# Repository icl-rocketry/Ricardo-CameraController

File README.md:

# Ricardo-CameraController
The CM5 (Compute Module 5) carrier board for cameras on rocket

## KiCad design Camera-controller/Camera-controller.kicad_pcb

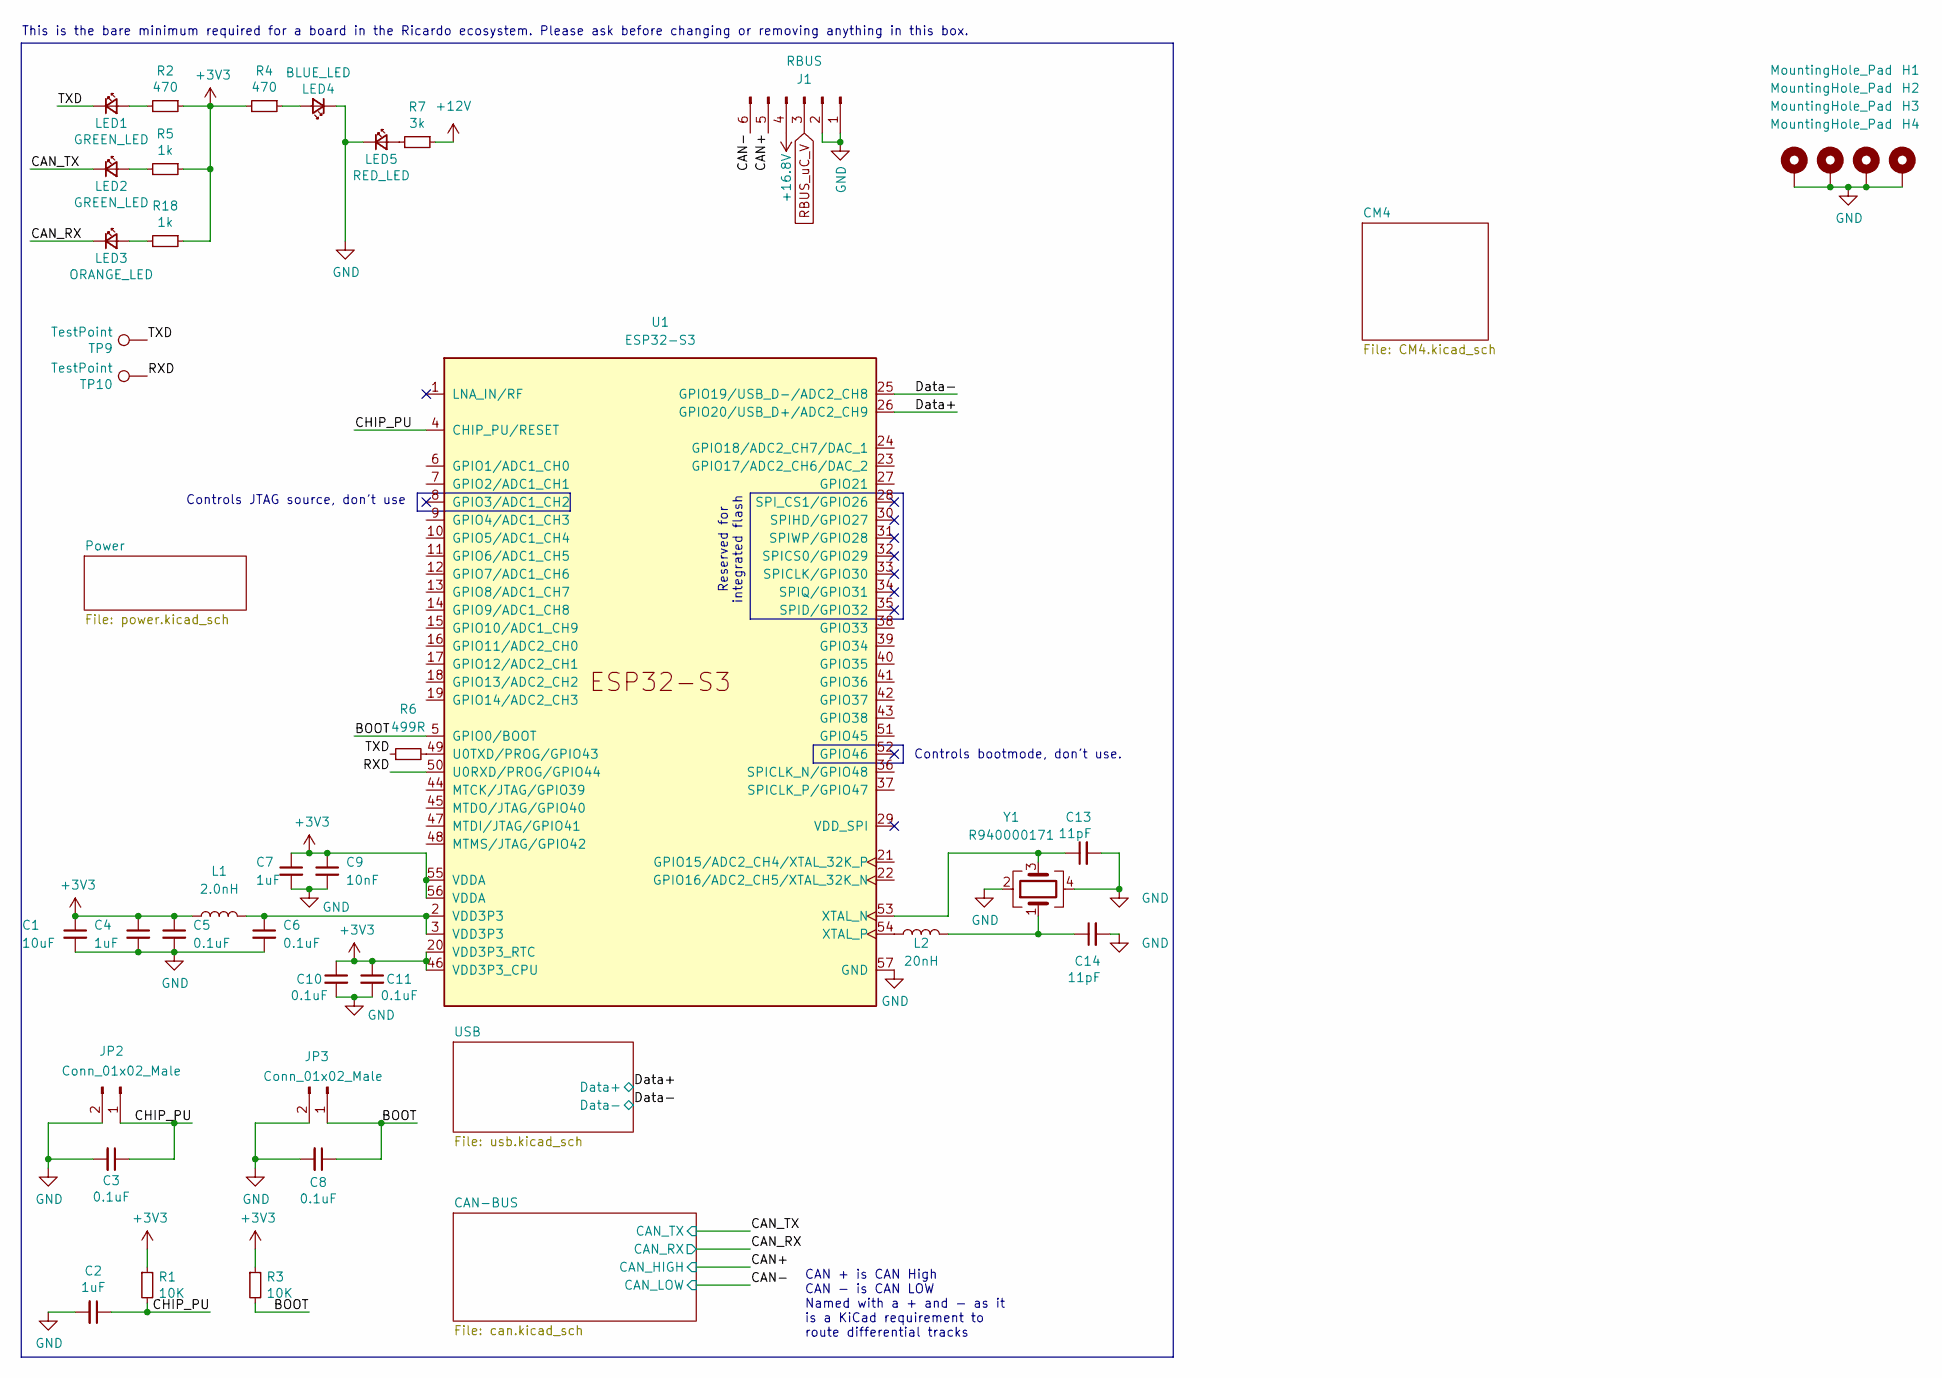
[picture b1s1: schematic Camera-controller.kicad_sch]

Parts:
C1: 10uF; C_0402_1005Metric
C2, C4, C7: 1uF; C_0402_1005Metric
C3, C5, C6, C8, C10, C11: 0.1uF; C_0402_1005Metric
C9: 10nF; C_0402_1005Metric
C13, C14: 11pF; C_0402_1005Metric
H1, H2, H3, H4: MountingHole_Pad; MountingHole_3.2mm_M3_DIN965_Pad
J1: RBUS; Molex_Mini-Fit_Jr_5569-06A2_2x03_P4.20mm_Horizontal
JP2, JP3: Conn_01x02_Male; PinHeader_1x02_P2.54mm_Vertical
L1: 2.0nH; L_0402_1005Metric
L2: 20nH; L_0402_1005Metric
LED1, LED2: GREEN_LED; LED_0402_1005Metric
LED3: ORANGE_LED; LED_0402_1005Metric
LED4: BLUE_LED; LED_0402_1005Metric
LED5: RED_LED; LED_0402_1005Metric
R1, R3: 10K; R_0402_1005Metric
R2, R4: 470; R_0402_1005Metric
R5, R18: 1k; R_0402_1005Metric
R6: 499R; R_0402_1005Metric
R7: 3k; R_0402_1005Metric
TP9, TP10: TestPoint; TestPoint_Pad_D1.0mm
U1: ESP32-S3; QFN40P700X700X90-57N
Y1: R940000171; Crystal_SMD_2016-4Pin_2.0x1.6mm

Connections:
+3V3: C1.1, C4.1, C5.1, C7.1, C9.1, C10.1, C11.1, L1.1, R1.1, R2.1, R3.1, R4.2, R5.1, R18.1, U1.20 (VDD3P3_RTC), U1.46 (VDD3P3_CPU), U1.55 (VDDA), U1.56 (VDDA); also elsewhere on the board
+12V: R7.1
/BOOT: C8.1, JP3.1, R3.2, U1.5 (GPIO0/BOOT)
/CAN+: J1.5; also elsewhere on the board
/CAN-: J1.6; also elsewhere on the board
/CAN_RX: LED3.1 (K); also elsewhere on the board
/CAN_TX: LED2.1 (K); also elsewhere on the board
/CHIP_PU: C2.1, C3.1, JP2.1, R1.2, U1.4 (CHIP_PU/RESET)
/Data+: U1.26 (GPIO20/USB_D+/ADC2_CH9); also elsewhere on the board
/Data-: U1.25 (GPIO19/USB_D-/ADC2_CH8); also elsewhere on the board
/RXD: TP10.1, U1.50 (U0RXD/PROG/GPIO44)
/TXD: LED1.1 (K), R6.1, TP9.1
unnamed: C6.1, L1.2, U1.2 (VDD3P3), U1.3 (VDD3P3)
unnamed: C14.1, L2.2, Y1.1
unnamed: LED1.2 (A), R2.2
unnamed: LED2.2 (A), R5.2
unnamed: LED3.2 (A), R18.2
unnamed: LED4.2 (A), R4.1
unnamed: LED5.2 (A), R7.2
unnamed: R6.2, U1.49 (U0TXD/PROG/GPIO43)
unnamed: C13.1, U1.53 (XTAL_N), Y1.3
unnamed: L2.1, U1.54 (XTAL_P)
RBUS_uC_V: J1.3; also elsewhere on the board

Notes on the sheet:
Controls bootmode, don't use.
This is the bare minimum required for a board in the Ricardo ecosystem. Please ask before changing or removing anything in this box.
CAN + is CAN High CAN - is CAN LOW Named with a + and - as it is a KiCad requirement to route differential tracks
Controls JTAG source, don't use
Reserved for integrated flash

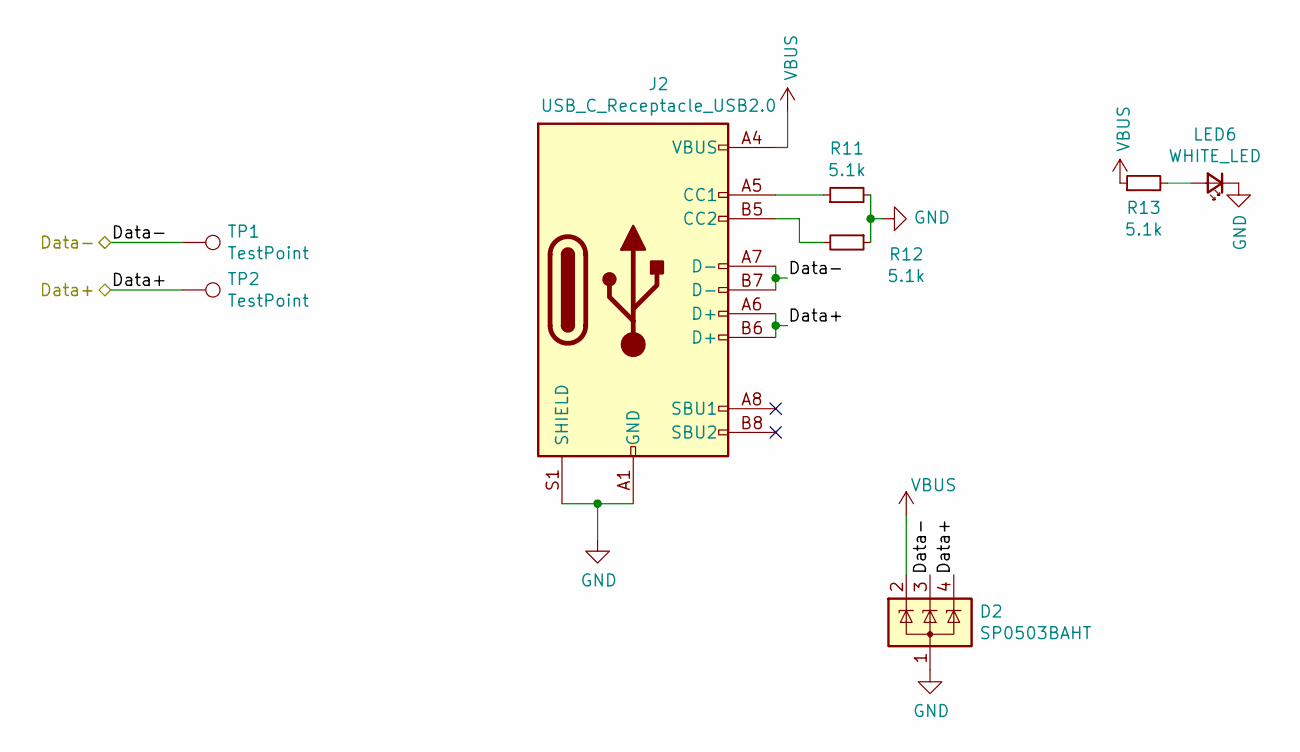
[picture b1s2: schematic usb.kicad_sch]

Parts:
D2: SP0503BAHT; SOT-143
J2: USB_C_Receptacle_USB2.0; USB_C_Receptacle_Palconn_UTC16-G
LED6: WHITE_LED; LED_0402_1005Metric
R11, R12, R13: 5.1k; R_0402_1005Metric
TP1, TP2: TestPoint; TestPoint_Pad_D1.0mm

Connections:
/Data+: D2.4 (K), J2.A6 (D+), J2.B6 (D+), TP2.1; also elsewhere on the board
/Data-: D2.3 (K), J2.A7 (D-), J2.B7 (D-), TP1.1; also elsewhere on the board
unnamed: J2.A5 (CC1), R11.1
unnamed: J2.B5 (CC2), R12.2
unnamed: LED6.2 (A), R13.2

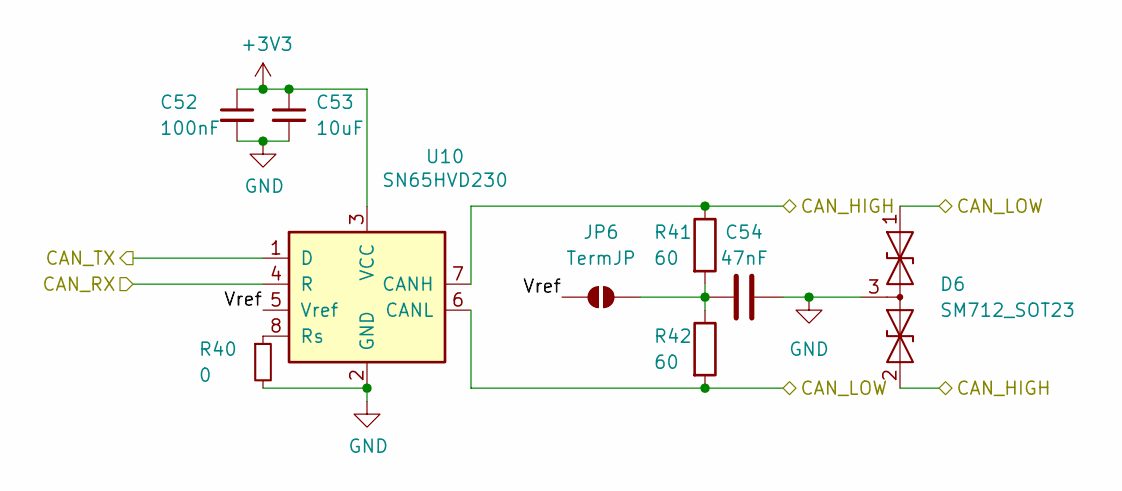
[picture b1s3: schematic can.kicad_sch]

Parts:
C52: 100nF; C_0402_1005Metric
C53: 10uF; C_0402_1005Metric
C54: 47nF; C_0402_1005Metric
D6: SM712_SOT23; SOT-23
JP6: TermJP; SmallerSolderJP
R40: 0; R_0603_1608Metric
R41, R42: 60; R_0603_1608Metric
U10: SN65HVD230; SOIC-8_3.9x4.9mm_P1.27mm

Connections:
unnamed 187: U10.1 (BST); also elsewhere on the board
unnamed 188: D6.1 (A1), R42.2, U10.6 (COMP); also elsewhere on the board
unnamed 189: U10.4 (SS); also elsewhere on the board

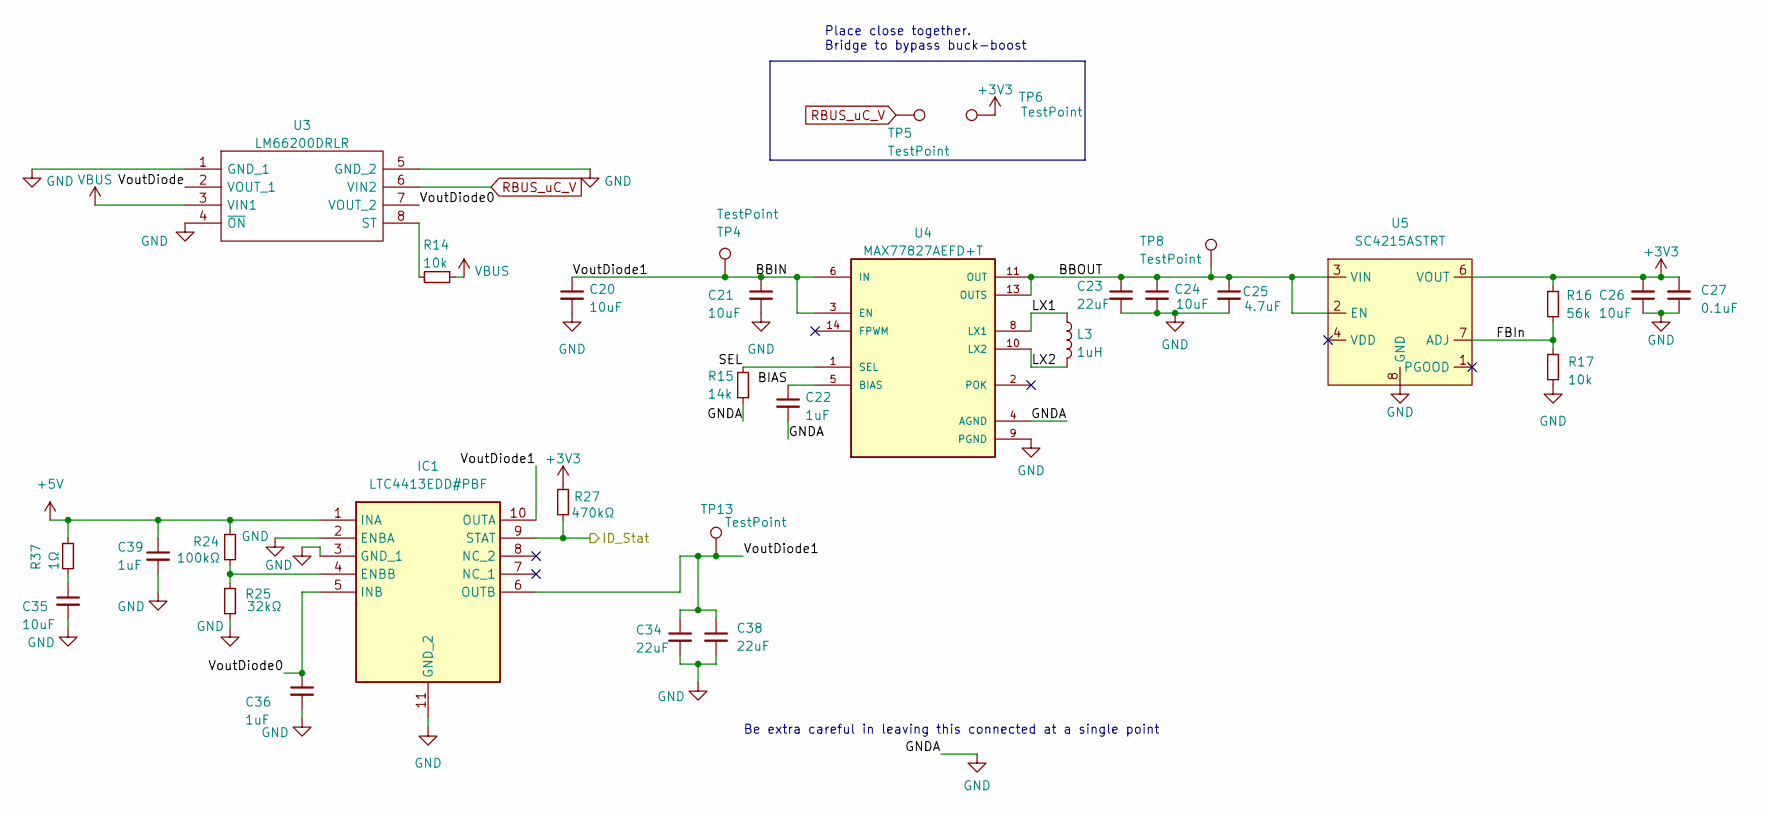
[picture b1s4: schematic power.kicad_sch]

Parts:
C20, C24, C26, C35: 10uF; C_0402_1005Metric
C21: 10uF; C_0603_1608Metric
C22, C36, C39: 1uF; C_0402_1005Metric
C23: 22uF; C_0603_1608Metric
C25: 4.7uF; C_0402_1005Metric
C27: 0.1uF; C_0402_1005Metric
C34, C38: 22uF; C_0402_1005Metric
IC1: LTC4413EDD#PBF; SON50P300X300X80-11N-D; Mouser Part Number 584-LTC4413EDD#PBF
L3: 1uH; L_0805_2012Metric
R14, R17: 10k; R_0402_1005Metric
R15: 14k; R_0402_1005Metric
R16: 56k; R_0402_1005Metric
R24: 100kΩ; R_0402_1005Metric
R25: 32kΩ; R_0402_1005Metric
R27: 470kΩ; R_0402_1005Metric
R37: 1Ω; R_0402_1005Metric
TP4, TP5, TP6, TP8: TestPoint; TestPoint_Pad_D1.5mm
TP13: TestPoint; TestPoint_Pad_D1.0mm
U3: LM66200DRLR; SOTFL50P160X60-8N; Manufacturer_Part_Number LM66200DRLR; Mouser Part Number 595-LM66200DRLR
U4: MAX77827AEFD+T; CONV_MAX77827AEFD+T; PARTREV B
U5: SC4215ASTRT; SOIC127P599X175-9N

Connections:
+3V3: C26.2, C27.2, R16.1, R27.1, TP6.1, U5.6 (VOUT); also elsewhere on the board
/Power/BBIN: C20.1, C21.1, C34.1, C38.1, IC1.6 (OUTB), IC1.10 (OUTA), TP4.1, TP13.1, U4.3 (EN), U4.6 (IN)
/Power/BBOUT: C23.1, C24.1, C25.1, TP8.1, U4.11 (OUT), U4.13 (OUTS), U5.2 (EN), U5.3 (VIN)
/Power/BIAS: C22.1, U4.5 (BIAS)
/Power/FBIn: R16.2, R17.1, U5.7 (ADJ)
/Power/ID_Stat: IC1.9 (STAT), R27.2
/Power/LX1: L3.1, U4.8 (LX1)
/Power/LX2: L3.2, U4.10 (LX2)
/Power/SEL: R15.1, U4.1 (SEL)
/Power/VoutDiode: U3.2 (VOUT_1)
/Power/VoutDiode0: C36.1, IC1.5 (INB), U3.7 (VOUT_2)
unnamed: C35.1, R37.2
unnamed: IC1.4 (ENBB), R24.2, R25.1
unnamed: R14.2, U3.8 (ST)
RBUS_uC_V: TP5.1, U3.6 (VIN2); also elsewhere on the board

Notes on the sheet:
Place close together. Bridge to bypass buck-boost
Be extra careful in leaving this connected at a single point

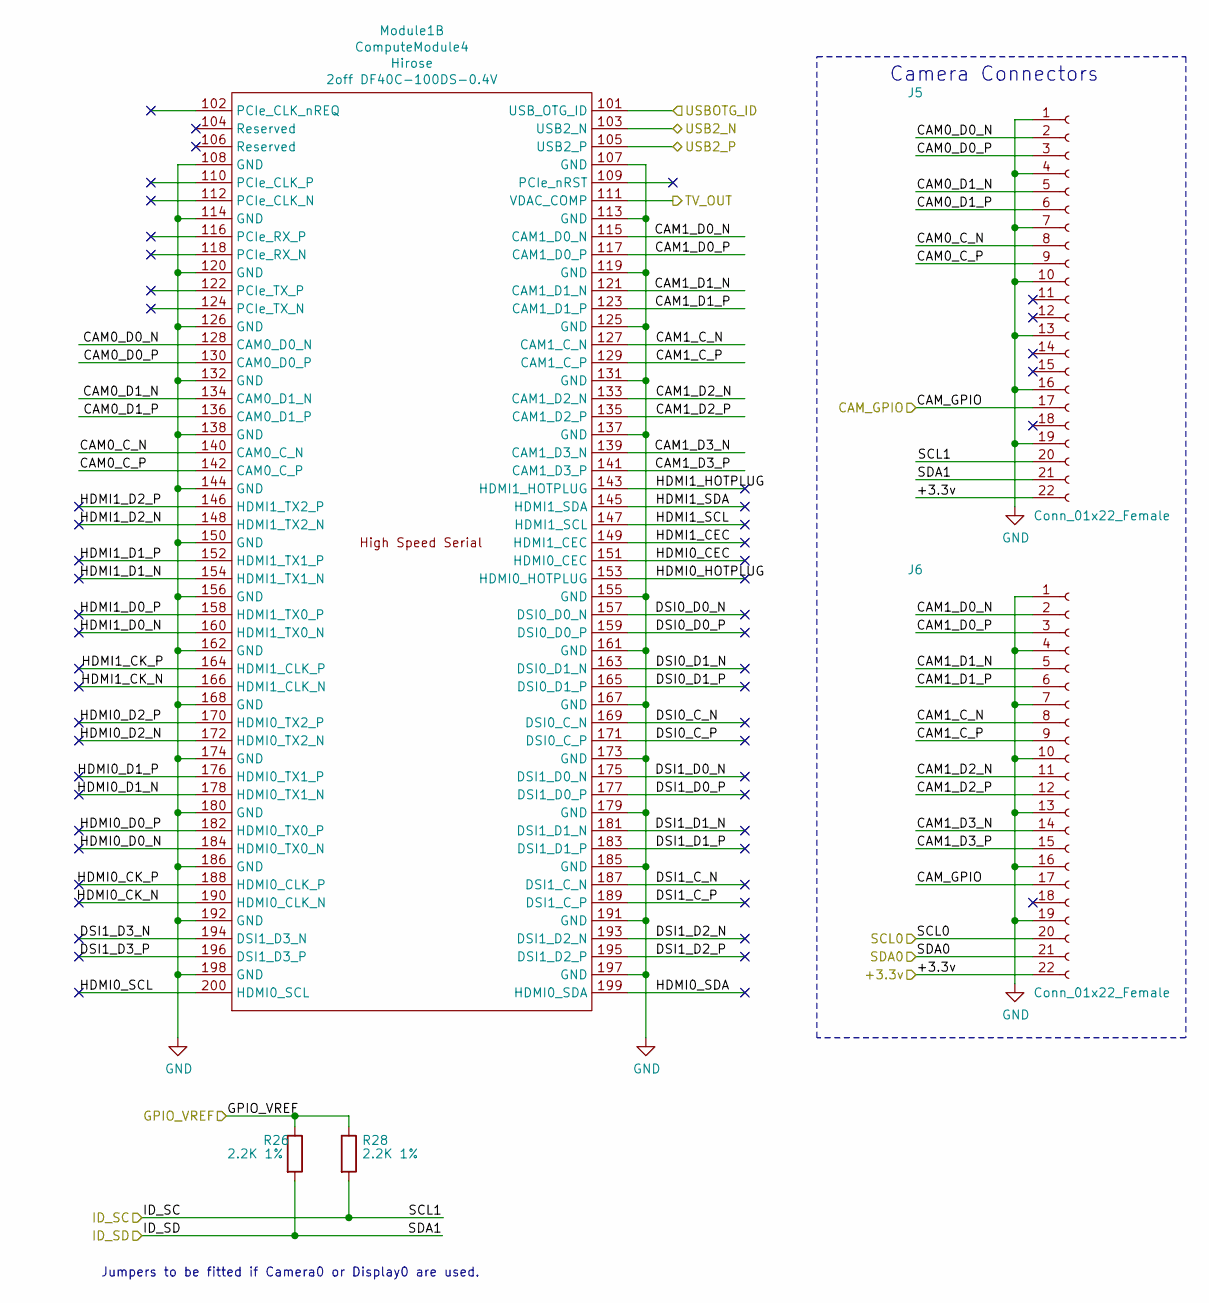
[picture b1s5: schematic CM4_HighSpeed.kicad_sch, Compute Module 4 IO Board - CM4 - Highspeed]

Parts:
J5, J6: Conn_01x22_Female; Hirose_FH12-22S-0.5SH_1x22-1MP_P0.50mm_Horizontal; Part Description 22 Position FFC, FPC Connector Contacts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
Module1: ComputeModule4; Raspberry-Pi-4-Compute-Module; Part Description 100 Position Connector Receptacle, Cent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
R26, R28: 2.2K 1%; R_0402_1005Metric; Part Description Resistor 2.2K M1005 1% 63mW

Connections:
/CM4/+3.3v: J5.22, J6.22; also elsewhere on the board
/CM4/CM4 _HighSpeed/CAM0_C_N: J5.8, Module1.140 (CAM0_C_N)
/CM4/CM4 _HighSpeed/CAM0_C_P: J5.9, Module1.142 (CAM0_C_P)
/CM4/CM4 _HighSpeed/CAM0_D0_N: J5.2, Module1.128 (CAM0_D0_N)
/CM4/CM4 _HighSpeed/CAM0_D0_P: J5.3, Module1.130 (CAM0_D0_P)
/CM4/CM4 _HighSpeed/CAM0_D1_N: J5.5, Module1.134 (CAM0_D1_N)
/CM4/CM4 _HighSpeed/CAM0_D1_P: J5.6, Module1.136 (CAM0_D1_P)
/CM4/CM4 _HighSpeed/CAM1_C_N: J6.8, Module1.127 (CAM1_C_N)
/CM4/CM4 _HighSpeed/CAM1_C_P: J6.9, Module1.129 (CAM1_C_P)
/CM4/CM4 _HighSpeed/CAM1_D0_N: J6.2, Module1.115 (CAM1_D0_N)
/CM4/CM4 _HighSpeed/CAM1_D0_P: J6.3, Module1.117 (CAM1_D0_P)
/CM4/CM4 _HighSpeed/CAM1_D1_N: J6.5, Module1.121 (CAM1_D1_N)
/CM4/CM4 _HighSpeed/CAM1_D1_P: J6.6, Module1.123 (CAM1_D1_P)
/CM4/CM4 _HighSpeed/CAM1_D2_N: J6.11, Module1.133 (CAM1_D2_N)
/CM4/CM4 _HighSpeed/CAM1_D2_P: J6.12, Module1.135 (CAM1_D2_P)
/CM4/CM4 _HighSpeed/CAM1_D3_N: J6.14, Module1.139 (CAM1_D3_N)
/CM4/CM4 _HighSpeed/CAM1_D3_P: J6.15, Module1.141 (CAM1_D3_P)
/CM4/CM4 _HighSpeed/CAM_GPIO: J5.17, J6.17; also elsewhere on the board
/CM4/CM4 _HighSpeed/DSI0_C_N: Module1.169 (DSI0_C_N)
/CM4/CM4 _HighSpeed/DSI0_C_P: Module1.171 (DSI0_C_P)
/CM4/CM4 _HighSpeed/DSI0_D0_N: Module1.157 (DSI0_D0_N)
/CM4/CM4 _HighSpeed/DSI0_D0_P: Module1.159 (DSI0_D0_P)
/CM4/CM4 _HighSpeed/DSI0_D1_N: Module1.163 (DSI0_D1_N)
/CM4/CM4 _HighSpeed/DSI0_D1_P: Module1.165 (DSI0_D1_P)
/CM4/CM4 _HighSpeed/DSI1_C_N: Module1.187 (DSI1_C_N)
/CM4/CM4 _HighSpeed/DSI1_C_P: Module1.189 (DSI1_C_P)
/CM4/CM4 _HighSpeed/DSI1_D0_N: Module1.175 (DSI1_D0_N)
/CM4/CM4 _HighSpeed/DSI1_D0_P: Module1.177 (DSI1_D0_P)
/CM4/CM4 _HighSpeed/DSI1_D1_N: Module1.181 (DSI1_D1_N)
/CM4/CM4 _HighSpeed/DSI1_D1_P: Module1.183 (DSI1_D1_P)
/CM4/CM4 _HighSpeed/DSI1_D2_N: Module1.193 (DSI1_D2_N)
/CM4/CM4 _HighSpeed/DSI1_D2_P: Module1.195 (DSI1_D2_P)
/CM4/CM4 _HighSpeed/DSI1_D3_N: Module1.194 (DSI1_D3_N)
/CM4/CM4 _HighSpeed/DSI1_D3_P: Module1.196 (DSI1_D3_P)
/CM4/CM4 _HighSpeed/GPIO_VREF: R26.1, R28.1; also elsewhere on the board
/CM4/CM4 _HighSpeed/HDMI0_CEC: Module1.151 (HDMI0_CEC)
/CM4/CM4 _HighSpeed/HDMI0_CK_N: Module1.190 (HDMI0_CLK_N)
/CM4/CM4 _HighSpeed/HDMI0_CK_P: Module1.188 (HDMI0_CLK_P)
/CM4/CM4 _HighSpeed/HDMI0_D0_N: Module1.184 (HDMI0_TX0_N)
/CM4/CM4 _HighSpeed/HDMI0_D0_P: Module1.182 (HDMI0_TX0_P)
/CM4/CM4 _HighSpeed/HDMI0_D1_N: Module1.178 (HDMI0_TX1_N)
/CM4/CM4 _HighSpeed/HDMI0_D1_P: Module1.176 (HDMI0_TX1_P)
/CM4/CM4 _HighSpeed/HDMI0_D2_N: Module1.172 (HDMI0_TX2_N)
/CM4/CM4 _HighSpeed/HDMI0_D2_P: Module1.170 (HDMI0_TX2_P)
/CM4/CM4 _HighSpeed/HDMI0_HOTPLUG: Module1.153 (HDMI0_HOTPLUG)
/CM4/CM4 _HighSpeed/HDMI0_SCL: Module1.200 (HDMI0_SCL)
/CM4/CM4 _HighSpeed/HDMI0_SDA: Module1.199 (HDMI0_SDA)
/CM4/CM4 _HighSpeed/HDMI1_CEC: Module1.149 (HDMI1_CEC)
/CM4/CM4 _HighSpeed/HDMI1_CK_N: Module1.166 (HDMI1_CLK_N)
/CM4/CM4 _HighSpeed/HDMI1_CK_P: Module1.164 (HDMI1_CLK_P)
/CM4/CM4 _HighSpeed/HDMI1_D0_N: Module1.160 (HDMI1_TX0_N)
/CM4/CM4 _HighSpeed/HDMI1_D0_P: Module1.158 (HDMI1_TX0_P)
/CM4/CM4 _HighSpeed/HDMI1_D1_N: Module1.154 (HDMI1_TX1_N)
/CM4/CM4 _HighSpeed/HDMI1_D1_P: Module1.152 (HDMI1_TX1_P)
/CM4/CM4 _HighSpeed/HDMI1_D2_N: Module1.148 (HDMI1_TX2_N)
/CM4/CM4 _HighSpeed/HDMI1_D2_P: Module1.146 (HDMI1_TX2_P)
/CM4/CM4 _HighSpeed/HDMI1_HOTPLUG: Module1.143 (HDMI1_HOTPLUG)
/CM4/CM4 _HighSpeed/HDMI1_SCL: Module1.147 (HDMI1_SCL)
/CM4/CM4 _HighSpeed/HDMI1_SDA: Module1.145 (HDMI1_SDA)
/CM4/CM4 _HighSpeed/ID_SC: J5.20, R28.2; also elsewhere on the board
/CM4/CM4 _HighSpeed/ID_SD: J5.21, R26.2; also elsewhere on the board
/CM4/CM4 _HighSpeed/SCL0: J6.20; also elsewhere on the board
/CM4/CM4 _HighSpeed/SDA0: J6.21; also elsewhere on the board
/CM4/CM4 _HighSpeed/USBOTG_ID: Module1.101 (USB_OTG_ID); also elsewhere on the board
/CM4/CM4_GPIO/TV_OUT: Module1.111 (VDAC_COMP); also elsewhere on the board
/CM4/CM4_USB/USB2_N: Module1.103 (USB2_N); also elsewhere on the board
/CM4/CM4_USB/USB2_P: Module1.105 (USB2_P); also elsewhere on the board

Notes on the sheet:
Jumpers to be fitted if Camera0 or Display0 are used.
Camera Connectors

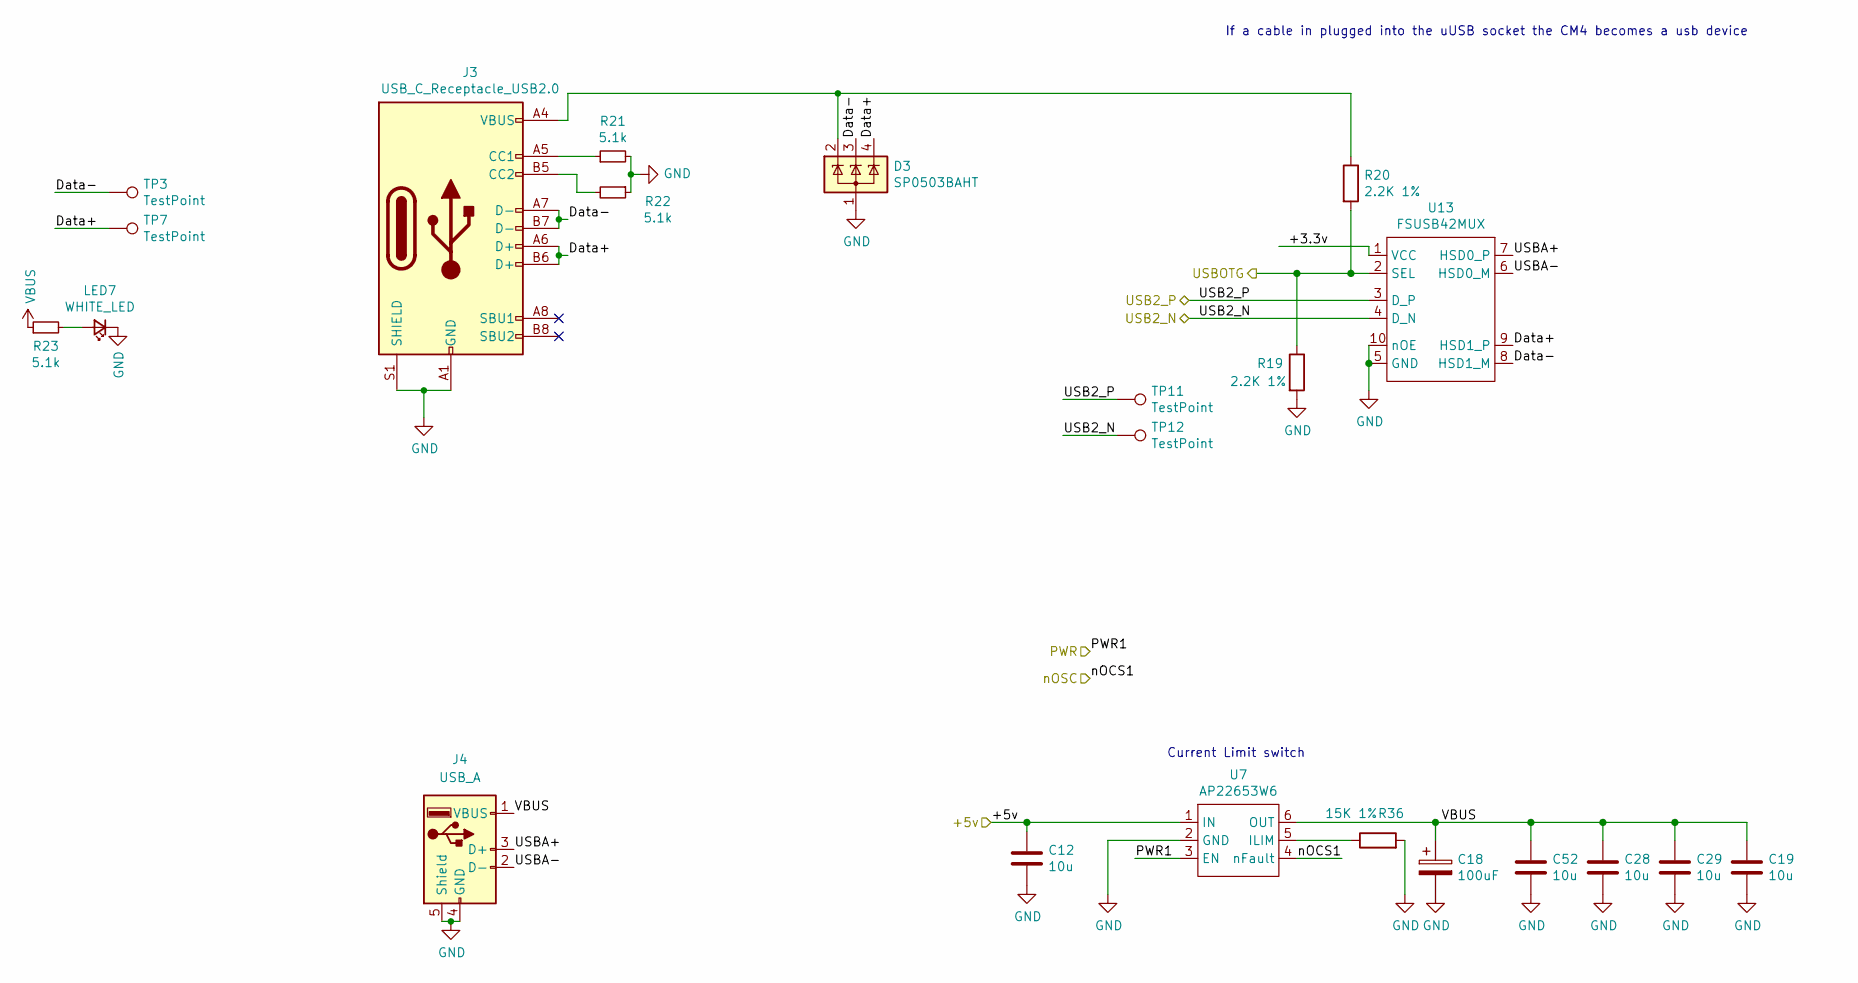
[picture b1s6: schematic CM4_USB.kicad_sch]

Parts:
C12, C19, C28, C29, C52: 10u; C_0805_2012Metric; Part Description 10uF 10% 10V Ceramic Capacitor X7R 0805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
C18: 100uF; CP_EIA-7343-31_Kemet-D; Part Description Capacitor, SP-Cap, 100u, 6.3V, 15mR ESR
D3: SP0503BAHT; SOT-143
J3: USB_C_Receptacle_USB2.0; USB_C_Receptacle_Palconn_UTC16-G
J4: USB_A; USB_A_Wuerth_614004134726_Horizontal
LED7: WHITE_LED; LED_0402_1005Metric
R19, R20: 2.2K 1%; R_0402_1005Metric; Part Description Resistor 2.2K M1005 1% 63mW
R21, R22, R23: 5.1k; R_0402_1005Metric
R36: 15K 1%; R_0402_1005Metric; Part Description Resistor 15K M1005 1% 63mW
TP3, TP7, TP11, TP12: TestPoint; TestPoint_Pad_D1.0mm
U7: AP22653W6; SOT-23-6; Part Description Power Switch/Driver 1:1 P-Channel 2.1A 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
U13: FSUSB42MUX; MSOP-10_3x3mm_P0.5mm; Part Description USB Switch IC 1 Channel 10-MSOP

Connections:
/CM4/CM4 _HighSpeed/USBOTG_ID: R19.1, R20.2, U13.2 (SEL); also elsewhere on the board
/CM4/CM4_USB/+3.3v: U13.1 (VCC)
/CM4/CM4_USB/Data+: D3.4 (K), J3.A6 (D+), J3.B6 (D+), TP7.1, U13.9 (HSD1_P)
/CM4/CM4_USB/Data-: D3.3 (K), J3.A7 (D-), J3.B7 (D-), TP3.1, U13.8 (HSD1_M)
/CM4/CM4_USB/PWR1: U7.3 (EN)
/CM4/CM4_USB/USB2_N: TP12.1, U13.4 (D_N); also elsewhere on the board
/CM4/CM4_USB/USB2_P: TP11.1, U13.3 (D_P); also elsewhere on the board
/CM4/CM4_USB/USBA+: J4.3 (D+), U13.7 (HSD0_P)
/CM4/CM4_USB/USBA-: J4.2 (D-), U13.6 (HSD0_M)
/CM4/CM4_USB/nOCS1: U7.4 (nFault)
unnamed: D3.2 (K), J3.A4 (VBUS), J3.A9 (VBUS), J3.B4 (VBUS), J3.B9 (VBUS), R20.1
unnamed: J3.A5 (CC1), R21.1
unnamed: J3.B5 (CC2), R22.2
unnamed: LED7.2 (A), R23.2
unnamed: R36.1, U7.5 (ILIM)

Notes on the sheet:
If a cable in plugged into the uUSB socket the CM4 becomes a usb device
Current Limit switch

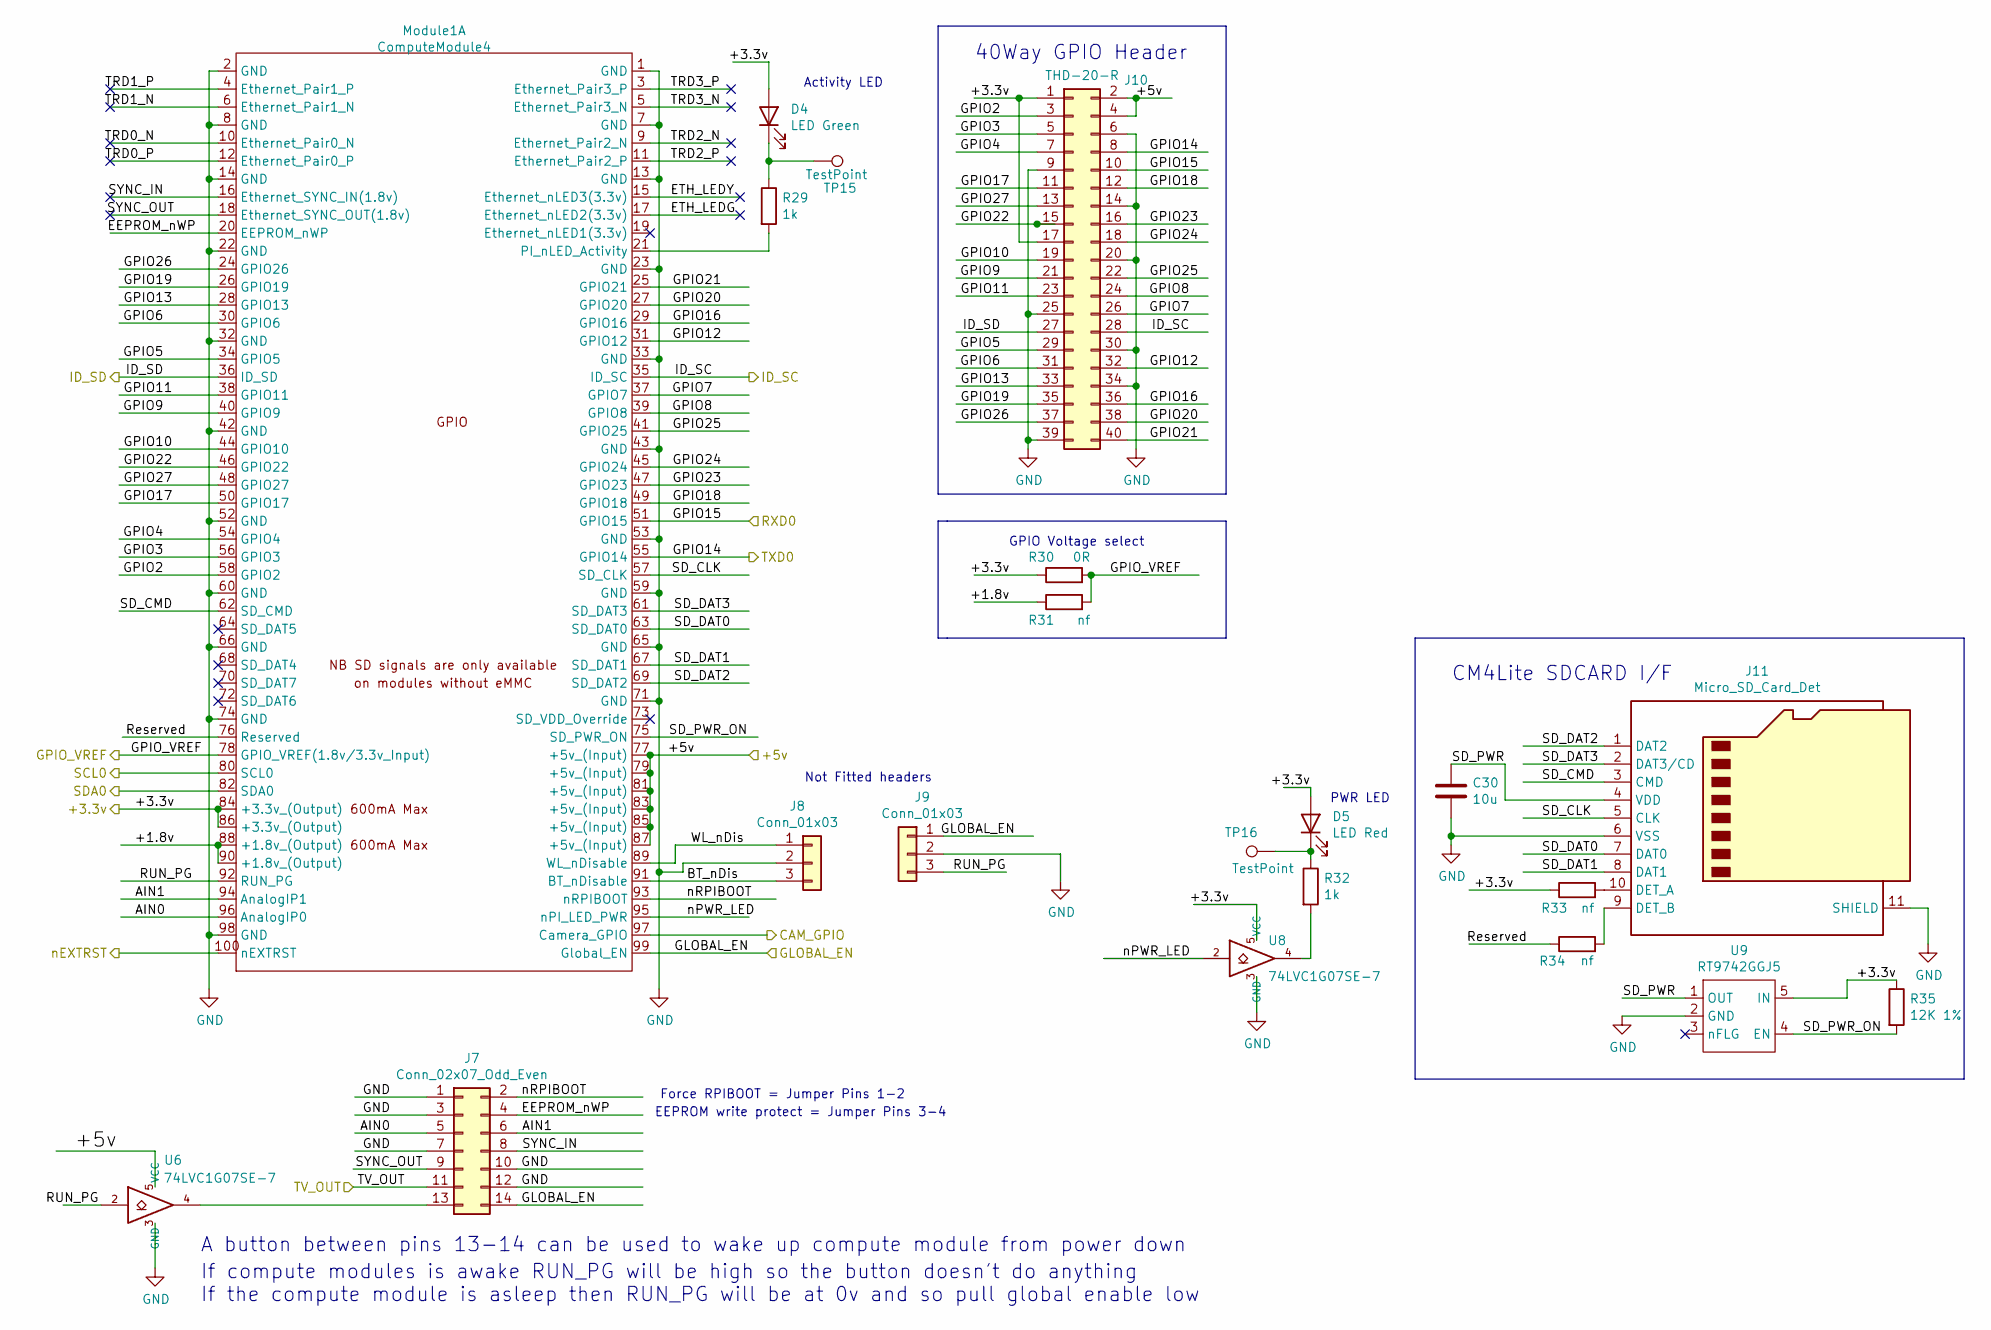
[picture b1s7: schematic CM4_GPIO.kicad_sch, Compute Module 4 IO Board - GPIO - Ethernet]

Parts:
C30: 10u; C_0805_2012Metric; Part Description 10uF 10% 10V Ceramic Capacitor X7R 0805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
D4: LED Green; LED_0603_1608Metric; Part Description Green 572nm LED Indication - Discrete 2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
D5: LED Red; LED_0603_1608Metric; Part Description Red 620nm LED Indication - Discrete 2.2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
J7: Conn_02x07_Odd_Even; PinHeader_2x07_P2.54mm_Vertical; Part Description PinHeader_2x07_P2.54mm_Vertical
J8, J9: Conn_01x03; PinHeader_1x03_P2.54mm_Vertical; Part Description 3pin 0.1" connector
J10: THD-20-R; PinHeader_2x20_P2.54mm_Vertical; Part Description PinHeader_2x20_P2.54mm_Vertical
J11: Micro_SD_Card_Det; SDCARD_MOLEX_503398-1892; Part Description 9 (8 + 1) Position Card Connector micro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
Module1: ComputeModule4; Raspberry-Pi-4-Compute-Module; Part Description 100 Position Connector Receptacle, Cent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
R29, R32: 1k; R_0402_1005Metric; Part Description Resistor 1K M1005 1% 63mW
R30: 0R; R_0402_1005Metric; Part Description Resistor 0R M2012 5%
R31: nf; R_0402_1005Metric
R33, R34: nf; R_0402_1005Metric; Part Description Resistor 1K M1005 1% 63mW
R35: 12K 1%; R_0402_1005Metric; Part Description Resistor 12K M1005 1% 63mW
TP15, TP16: TestPoint; TestPoint_Pad_2.0x2.0mm
U6, U8: 74LVC1G07SE-7; SOT-353_SC-70-5; Part Description Buffer, Non-Inverting 1 Element 1 Bit p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
U9: RT9742GGJ5; SOT-23-5; Part Description Power Switch/Driver 1:1 N-Channel 1A TS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

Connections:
/CM4/+3.3v: D4.2 (A), D5.2 (A), J10.1, J10.17, Module1.84 (+3.3v_(Output)), Module1.86 (+3.3v_(Output)), R30.1, R33.1, R35.1, U8.5 (VCC), U9.5 (IN); also elsewhere on the board
/CM4/CM4 _HighSpeed/CAM_GPIO: Module1.97 (Camera_GPIO); also elsewhere on the board
/CM4/CM4 _HighSpeed/GPIO_VREF: Module1.78 (GPIO_VREF(1.8v/3.3v_Input)), R30.2, R31.2; also elsewhere on the board
/CM4/CM4 _HighSpeed/ID_SC: J10.28, Module1.35 (ID_SC); also elsewhere on the board
/CM4/CM4 _HighSpeed/ID_SD: J10.27, Module1.36 (ID_SD); also elsewhere on the board
/CM4/CM4 _HighSpeed/SCL0: Module1.80 (SCL0); also elsewhere on the board
/CM4/CM4 _HighSpeed/SDA0: Module1.82 (SDA0); also elsewhere on the board
/CM4/CM4_GPIO/+1.8v: Module1.88 (+1.8v_(Output)), Module1.90 (+1.8v_(Output)), R31.1
/CM4/CM4_GPIO/AIN0: J7.5, Module1.96 (AnalogIP0)
/CM4/CM4_GPIO/AIN1: J7.6, Module1.94 (AnalogIP1)
/CM4/CM4_GPIO/BT_nDis: J8.3, Module1.91 (BT_nDisable)
/CM4/CM4_GPIO/EEPROM_nWP: J7.4, Module1.20 (EEPROM_nWP)
/CM4/CM4_GPIO/ETH_LEDG: Module1.17 (Ethernet_nLED2(3.3v))
/CM4/CM4_GPIO/ETH_LEDY: Module1.15 (Ethernet_nLED3(3.3v))
/CM4/CM4_GPIO/GLOBAL_EN: J7.14, J9.1, Module1.99 (Global_EN)
/CM4/CM4_GPIO/GPIO2: J10.3, Module1.58 (GPIO2)
/CM4/CM4_GPIO/GPIO3: J10.5, Module1.56 (GPIO3)
/CM4/CM4_GPIO/GPIO4: J10.7, Module1.54 (GPIO4)
/CM4/CM4_GPIO/GPIO5: J10.29, Module1.34 (GPIO5)
/CM4/CM4_GPIO/GPIO6: J10.31, Module1.30 (GPIO6)
/CM4/CM4_GPIO/GPIO7: J10.26, Module1.37 (GPIO7)
/CM4/CM4_GPIO/GPIO8: J10.24, Module1.39 (GPIO8)
/CM4/CM4_GPIO/GPIO9: J10.21, Module1.40 (GPIO9)
/CM4/CM4_GPIO/GPIO10: J10.19, Module1.44 (GPIO10)
/CM4/CM4_GPIO/GPIO11: J10.23, Module1.38 (GPIO11)
/CM4/CM4_GPIO/GPIO12: J10.32, Module1.31 (GPIO12)
/CM4/CM4_GPIO/GPIO13: J10.33, Module1.28 (GPIO13)
/CM4/CM4_GPIO/GPIO14: J10.8, Module1.55 (GPIO14)
/CM4/CM4_GPIO/GPIO15: J10.10, Module1.51 (GPIO15)
/CM4/CM4_GPIO/GPIO16: J10.36, Module1.29 (GPIO16)
/CM4/CM4_GPIO/GPIO17: J10.11, Module1.50 (GPIO17)
/CM4/CM4_GPIO/GPIO18: J10.12, Module1.49 (GPIO18)
/CM4/CM4_GPIO/GPIO19: J10.35, Module1.26 (GPIO19)
/CM4/CM4_GPIO/GPIO20: J10.38, Module1.27 (GPIO20)
/CM4/CM4_GPIO/GPIO21: J10.40, Module1.25 (GPIO21)
/CM4/CM4_GPIO/GPIO22: J10.15, Module1.46 (GPIO22)
/CM4/CM4_GPIO/GPIO23: J10.16, Module1.47 (GPIO23)
/CM4/CM4_GPIO/GPIO24: J10.18, Module1.45 (GPIO24)
/CM4/CM4_GPIO/GPIO25: J10.22, Module1.41 (GPIO25)
/CM4/CM4_GPIO/GPIO26: J10.37, Module1.24 (GPIO26)
/CM4/CM4_GPIO/GPIO27: J10.13, Module1.48 (GPIO27)
/CM4/CM4_GPIO/RUN_PG: J9.3, Module1.92 (RUN_PG), U6.2
/CM4/CM4_GPIO/Reserved: Module1.76 (Reserved), R34.1
/CM4/CM4_GPIO/SD_CLK: J11.5 (CLK), Module1.57 (SD_CLK)
/CM4/CM4_GPIO/SD_CMD: J11.3 (CMD), Module1.62 (SD_CMD)
/CM4/CM4_GPIO/SD_DAT0: J11.7 (DAT0), Module1.63 (SD_DAT0)
/CM4/CM4_GPIO/SD_DAT1: J11.8 (DAT1), Module1.67 (SD_DAT1)
/CM4/CM4_GPIO/SD_DAT2: J11.1 (DAT2), Module1.69 (SD_DAT2)
/CM4/CM4_GPIO/SD_DAT3: J11.2 (DAT3/CD), Module1.61 (SD_DAT3)
/CM4/CM4_GPIO/SD_PWR: C30.1, J11.4 (VDD), U9.1 (OUT)
/CM4/CM4_GPIO/SD_PWR_ON: Module1.75 (SD_PWR_ON), R35.2, U9.4 (EN)
/CM4/CM4_GPIO/SYNC_IN: J7.8, Module1.16 (Ethernet_SYNC_IN(1.8v))
/CM4/CM4_GPIO/SYNC_OUT: J7.9, Module1.18 (Ethernet_SYNC_OUT(1.8v))
/CM4/CM4_GPIO/TRD0_N: Module1.10 (Ethernet_Pair0_N)
/CM4/CM4_GPIO/TRD0_P: Module1.12 (Ethernet_Pair0_P)
/CM4/CM4_GPIO/TRD1_N: Module1.6 (Ethernet_Pair1_N)
/CM4/CM4_GPIO/TRD1_P: Module1.4 (Ethernet_Pair1_P)
/CM4/CM4_GPIO/TRD2_N: Module1.9 (Ethernet_Pair2_N)
/CM4/CM4_GPIO/TRD2_P: Module1.11 (Ethernet_Pair2_P)
/CM4/CM4_GPIO/TRD3_N: Module1.5 (Ethernet_Pair3_N)
/CM4/CM4_GPIO/TRD3_P: Module1.3 (Ethernet_Pair3_P)
/CM4/CM4_GPIO/TV_OUT: J7.11; also elsewhere on the board
/CM4/CM4_GPIO/WL_nDis: J8.1, Module1.89 (WL_nDisable)
/CM4/CM4_GPIO/nEXTRST: Module1.100 (nEXTRST)
/CM4/CM4_GPIO/nPWR_LED: Module1.95 (nPI_LED_PWR), U8.2
/CM4/CM4_GPIO/nRPIBOOT: J7.2, Module1.93 (nRPIBOOT)
unnamed: D4.1 (K), R29.1, TP15.1
unnamed: D5.1 (K), R32.1, TP16.1
unnamed: J7.13, U6.4
unnamed: J11.10 (DET_A), R33.2
unnamed: J11.9 (DET_B), R34.2
unnamed: Module1.21 (PI_nLED_Activity), R29.2
unnamed: R32.2, U8.4

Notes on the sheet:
PWR LED
40Way GPIO Header
CM4Lite SDCARD I/F
GPIO Voltage select
Activity LED
EEPROM write protect = Jumper Pins 3-4
Not Fitted headers
A button between pins 13-14 can be used to wake up compute module from power down
If compute modules is awake RUN_PG will be high so the button doesn't do anything If the compute module is asleep then RUN_PG will be at 0v and so pull global enable low
Force RPIBOOT = Jumper Pins 1-2

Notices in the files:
Camera-controller/CM4_GPIO.kicad_sch:
© 2020-2022 Raspberry Pi Ltd (formerly Raspberry Pi (Trading) Ltd.)
